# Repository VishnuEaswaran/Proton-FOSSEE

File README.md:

# Proton-FOSSEE

Proton is an arduino based development board with a battery of on-board sensors and actuators bundled with provisions for multiple communication technologies. Designed to be a one-stop solution for prototyping, it could serve as a playground for hardware novices as well as seasoned developers. 

P.S. : Proton ~~is~~ was  a project developed for FOSSEE of IIT bombay. The project is ~~in active development and thus watch this space for latest updates.~~ discontinued.

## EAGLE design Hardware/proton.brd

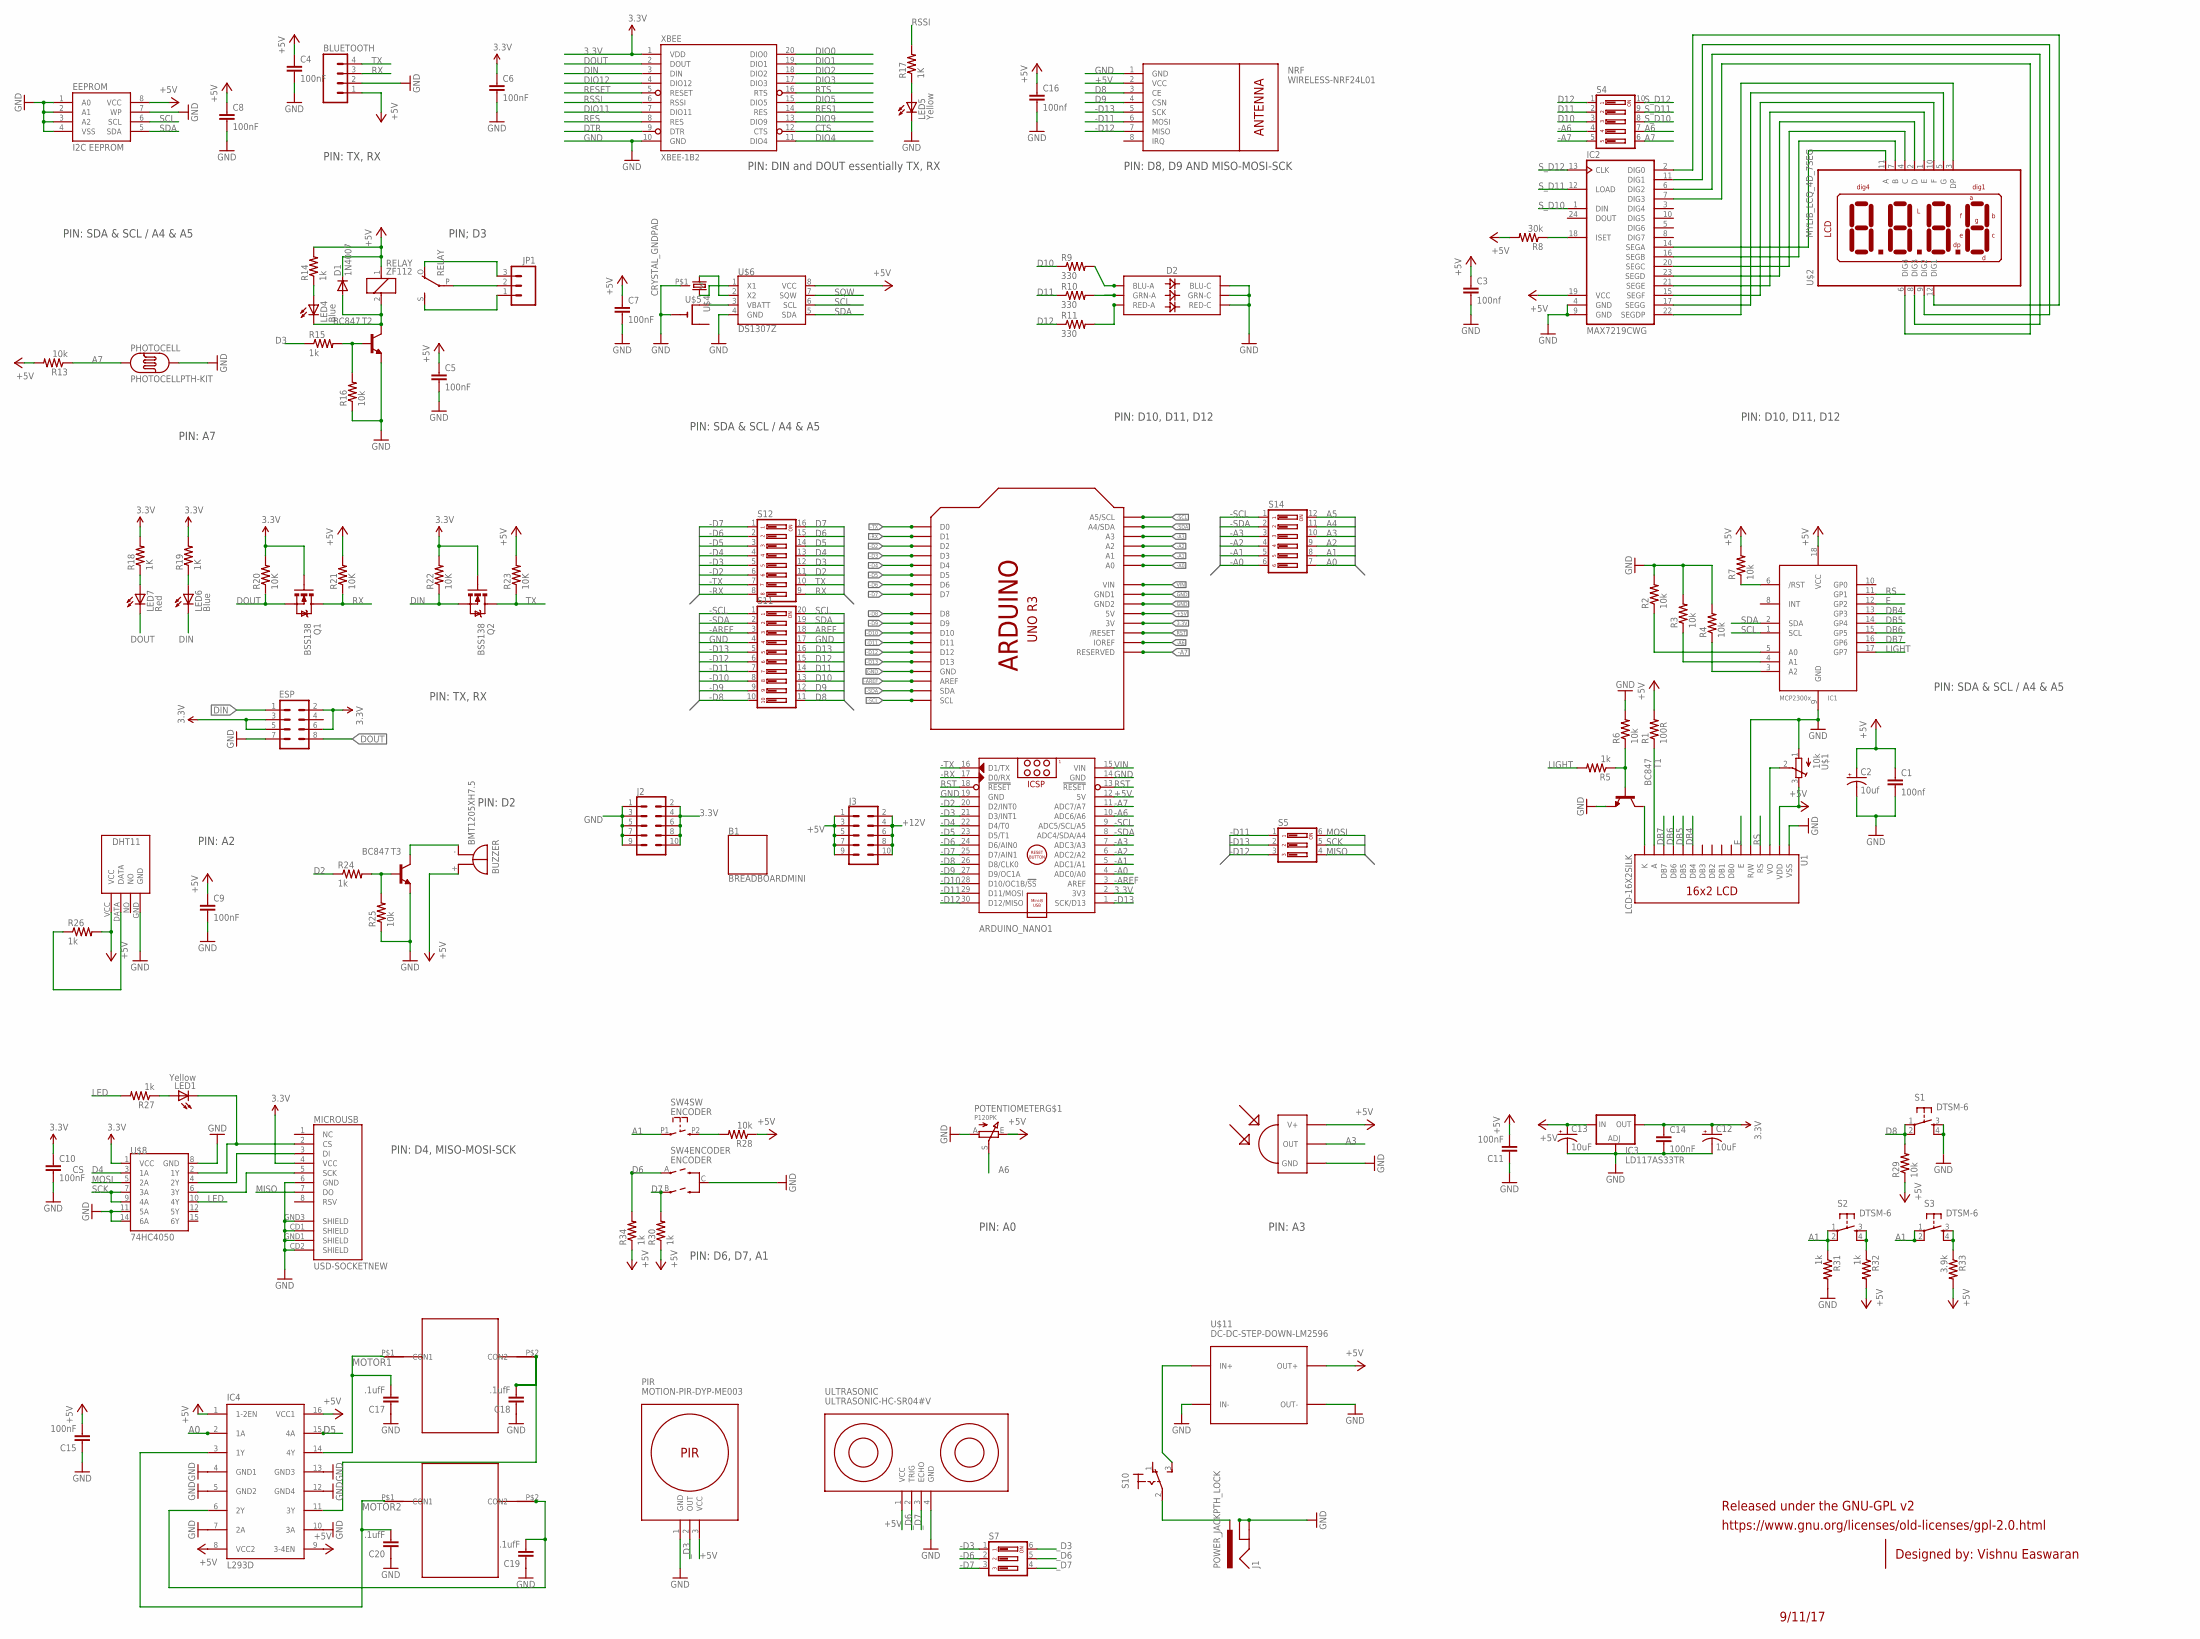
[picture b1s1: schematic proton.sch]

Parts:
ARDUINO_NANO1: ARDUINO_NANO
B1: BREADBOARDMINI; BREADBOARD-MINI
BLUETOOTH: M04PTH; 1X04
BUZZER: BMT1205XH7.5
C1, C3, C16: 100nf; 0805
C2: 10uf; EIA3216
C4, C5, C6, C7, C8, C9, C10, C11, C14, C15: 100nF; 0805
C12, C13: 10uF; EIA3216
C17, C18, C19, C20: .1ufF; 0805
D1: 1N4007; SMA-DIODE_ALT
D2: LED-RGBNO_IC; LED-TRICOLOR-5050
EEPROM: I2C EEPROM; SO08-EIAJ
ESP: M04X2; 2X4
IC1: MCP2300X/SO; SO18W
IC2: MAX7219CWG; SO24W
IC3: LD117AS33TR; SOT223
IC4: L293D; DIL16
IR: TSOP1730; TSOP17XX
J1: POWER_JACKPTH_LOCK; POWER_JACK_PTH_LOCK
J2, J3: CONN_05X2NO_SILK; 2X5_NOSILK
JP1: M03-SCREW-5MM; SCREWTERMINAL-5MM-3
LED1, LED5: Yellow; CHIPLED_0805
LED4, LED6: Blue; CHIPLED_0805
LED7: Red; CHIPLED_0805
MICROUSB: USD-SOCKETNEW; MICRO-SD-SOCKET-PP
MOTOR1, MOTOR2: TOY_MOTOR
NRF: WIRELESS-NRF24L01
PHOTOCELL: PHOTOCELLPTH-KIT; PHOTOCELL-KIT
PIR: MOTION-PIR-DYP-ME003
POTENTIOMETER: P120PK
Q1, Q2: BSS138; SOT23-3
R1: 100R; 0805
R2, R3, R4, R6, R7, R13, R16, R25, R28, R29: 10k; 0805
R5, R14, R15, R24, R26, R27, R30, R31, R32, R34: 1k; 0805
R8: 30k; 0805
R9, R10, R11: 330; 0805
R17, R18, R19: 1K; 0805
R20, R21, R22, R23: 10K; 0805
R33: 3.9k; 0805
RELAY: ZF112
S1, S2, S3: DTSM-6
S4: DIP05YL
S5, S7: DIP03YL
S10: M9040P
S11: DIP10YL
S12: DIP08YL
S14: DIP06YL
SW4: ENCODER; PEC12_INCREMENTAL_ENCODER
T1, T2, T3: BC847; SOT23-BEC
TEMPERATURESENSOR: DHT11
U1: LCD-16X2SILK; LCD-16X2
U$1: 10k; TC33X
U$2: MYLIB_LCQ_4D_7SEG; MYLIB_LDQ_4D_7SEG
U$4: CRYSTAL_GNDPAD; TC38H_GNDPAD
U$5: CR1220SMT; CR1220-SMD
U$6: DS1307Z; SO08-0.15
U$8: 74HC4050; SO016
U$11: DC-DC-STEP-DOWN-LM2596
U$14: UNO_R3
ULTRASONIC: ULTRASONIC-HC-SR04#V
XBEE: XBEE-1B2; XBEE-SILK

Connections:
3.3V: ARDUINO_NANO1.2 (3V3), C6.1, C10.1, C12.A (+), C14.1, ESP.2, ESP.3, ESP.5, ESP.6, IC3.4 (OUT), J2.2, J2.4, J2.6, J2.8, J2.10, MICROUSB.4 (VCC), Q1.1 (G), Q2.1 (G), R18.2, R19.2, R20.2, R22.2, U$8.1 (VCC), U$14.3V, XBEE.1 (VDD)
+5V: ARDUINO_NANO1.12 (5V), BLUETOOTH.1, BUZZER.+, C1.1, C2.A (+), C3.1, C4.1, C5.1, C7.1, C8.1, C9.1, C11.2, C13.A (+), C15.2, C16.1, D1.C, EEPROM.8 (VCC), IC1.18 (VCC), IC2.19 (VCC), IC3.3 (IN), IC4.1 (1-2EN), IC4.8 (VCC2), IC4.9 (3-4EN), IC4.16 (VCC1), IR.V+, J3.1, J3.3, J3.5, J3.7, J3.9, NRF.2 (VCC), PIR.3 (VCC), POTENTIOMETER.E, R1.2, R7.2, R8.2, R13.2, R14.2, R21.2, R23.2, R26.2, R28.1, R29.1, R30.1, R32.2, R33.2, R34.1, RELAY.1, TEMPERATURESENSOR.VCC, U1.2 (VDD), U$1.3 (E), U$6.8 (VCC), U$11.OUT+, U$14.5V, ULTRASONIC.1 (VCC)
+12V: J1.PWR, J3.2, J3.4, J3.6, J3.8, J3.10, S10.2
-A0: ARDUINO_NANO1.4 (ADC0/A0), S14.6, U$14.A0
-A1: ARDUINO_NANO1.5 (ADC1/A1), S14.5, U$14.A1
-A2: ARDUINO_NANO1.6 (ADC2/A2), S14.4, U$14.A2
-A3: ARDUINO_NANO1.7 (ADC3/A3), S14.3, U$14.A3
-A6: ARDUINO_NANO1.10 (ADC6/A6), S4.4, U$14.IOREF
-A7: ARDUINO_NANO1.11 (ADC7/A7), S4.5, U$14.RESERVED
-AREF: ARDUINO_NANO1.3 (AREF), S11.3, U$14.AREF
-D2: ARDUINO_NANO1.20 (D2/INT0), S12.6, U$14.D2
-D3: ARDUINO_NANO1.21 (D3/INT1), S7.1, S12.5, U$14.D3
-D4: ARDUINO_NANO1.22 (D4/T0), S12.4, U$14.D4
-D5: ARDUINO_NANO1.23 (D5/T1), S12.3, U$14.D5
-D6: ARDUINO_NANO1.24 (D6/AIN0), S7.2, S12.2, U$14.D6
-D7: ARDUINO_NANO1.25 (D7/AIN1), S7.3, S12.1, U$14.D7
-D8: ARDUINO_NANO1.26 (D8/CLK0), S11.10, U$14.D8
-D9: ARDUINO_NANO1.27 (D9/OC1A), S11.9, U$14.D9
-D10: ARDUINO_NANO1.28 (D10/OC1B/!SS), S11.8, U$14.D10
-D11: ARDUINO_NANO1.29 (D11/MOSI), NRF.6 (MOSI), S5.1, S11.7, U$14.D11
-D12: ARDUINO_NANO1.30 (D12/MISO), NRF.7 (MISO), S5.3, S11.6, U$14.D12
-D13: ARDUINO_NANO1.1 (SCK/D13), NRF.5 (SCK), S5.2, S11.5, U$14.D13
-RX: ARDUINO_NANO1.17 (D0/RX), S12.8, U$14.D1
-SCL: ARDUINO_NANO1.9 (ADC5/SCL/A5), S11.1, S14.1, U$14.A5 (A5/SCL), U$14.SCL
-SDA: ARDUINO_NANO1.8 (ADC4/SDA/A4), S11.2, S14.2, U$14.A4 (A4/SDA), U$14.SDA
-TX: ARDUINO_NANO1.16 (D1/TX), S12.7, U$14.D0
A0: IC4.2 (1A), S14.7
A1: R31.1, S2.1, S2.2, S3.1, S3.2, S14.8, SW4.P1 (1)
A2: R26.1, S14.9, TEMPERATURESENSOR.DATA
A3: IR.OUT, S14.10
A4: S14.11
A5: S14.12
A6: POTENTIOMETER.S, S4.7
A7: PHOTOCELL.1, R13.1, S4.6
AREF: S11.18
CTS: XBEE.12 (CTS)
D2: R24.1, S12.11
D3: R15.1, S12.12
D4: S12.13, U$8.3 (1A)
D5: IC4.15 (4A), S12.14
D6: R34.2, S12.15, SW4.A
D7: R30.2, S12.16, SW4.B
D8: NRF.3 (CE), R29.2, S1.1, S1.2, S11.11
D9: NRF.4 (CSN), S11.12
D10: R9.1, S4.3, S11.13
D11: R10.1, S4.2, S11.14
D12: R11.1, S4.1, S11.15
D13: S11.16
DB4: IC1.13 (GP3), U1.11 (DB4)
DB5: IC1.14 (GP4), U1.12 (DB5)
DB6: IC1.15 (GP5), U1.13 (DB6)
DB7: IC1.16 (GP6), U1.14 (DB7)
DIN: ESP.1, LED6.C, Q2.2 (S), R22.1, XBEE.3 (DIN)
DIO0: XBEE.20 (DIO0)
DIO1: XBEE.19 (DIO1)
DIO2: XBEE.18 (DIO2)
DIO3: XBEE.17 (DIO3)
DIO4: XBEE.11 (DIO4)
DIO5: XBEE.15 (DIO5)
DIO9: XBEE.13 (DIO9)
DIO11: XBEE.7 (DIO11)
DIO12: XBEE.4 (DIO12)
DOUT: ESP.8, LED7.C, Q1.2 (S), R20.1, XBEE.2 (DOUT)
DTR: XBEE.9 (DTR)
E: IC1.12 (GP2), U1.6 (E)
GND: ARDUINO_NANO1.14 (GND), ARDUINO_NANO1.19 (GND), BLUETOOTH.2, C1.2, C2.C (-), C3.2, C4.2, C5.2, C6.2, C7.2, C8.2, C9.2, C10.2, C11.1, C12.C (-), C13.C (-), C14.2, C15.1, C16.2, C17.1, C18.1, C19.1, C20.1, D2.4 (BLU-C), D2.5 (RED-C), D2.6 (GRN-C), EEPROM.1 (A0), EEPROM.2 (A1), EEPROM.3 (A2), EEPROM.4 (VSS), EEPROM.7 (WP), ESP.7, IC1.9 (GND), IC2.4 (GND), IC2.9 (GND), IC3.1 (ADJ), IC4.4 (GND1), IC4.5 (GND2), IC4.7 (2A), IC4.10 (3A), IC4.12 (GND4), IC4.13 (GND3), IR.GND, J1.GND, J1.GNDBREAK, J2.1, J2.3, J2.5, J2.7, J2.9, LED5.C, MICROUSB.6 (GND), MICROUSB.CD1 (SHIELD), MICROUSB.CD2 (SHIELD), MICROUSB.GND1 (SHIELD), MICROUSB.GND3 (SHIELD), NRF.1 (GND), PHOTOCELL.2, PIR.1 (GND), POTENTIOMETER.A, R2.2, R3.2, R4.2, R6.2, R16.1, R25.1, R31.2, S1.3, S1.4, S11.4, S11.17, SW4.C, T1.E, T2.E, T3.E, TEMPERATURESENSOR.GND, U1.1 (VSS), U1.5 (R/W), U$1.1 (A), U$4.P$1 (3), U$5.-, U$6.4 (GND), U$8.8 (GND), U$8.11 (5A), U$8.14 (6A), U$11.IN-, U$11.OUT-, U$14.GND, U$14.GND1, U$14.GND2, ULTRASONIC.4 (GND), XBEE.10 (GND)
LED: R27.2, U$8.10 (4Y)
LIGHT: IC1.17 (GP7), R5.2
MISO: MICROUSB.7 (DO), S5.4
MOSI: S5.6, U$8.5 (2A)
MOTOR1: C17.2, IC4.14 (4Y), MOTOR1.P$1 (CON1)
MOTOR2: C20.2, IC4.3 (1Y), MOTOR2.P$1 (CON1)
unnamed: C19.2, IC4.6 (2Y), MOTOR2.P$2 (CON2)
unnamed: S10.3 (S), U$11.IN+
unnamed: D2.3 (BLU-A), R9.2
unnamed: R32.1, S2.3, S2.4
unnamed: D2.2 (RED-A), R11.2
unnamed: D2.1 (GRN-A), R10.2
unnamed: R24.2, R25.2, T3.B
unnamed: C18.2, IC4.11 (3Y), MOTOR1.P$2 (CON2)
unnamed: R33.1, S3.3, S3.4
unnamed: JP1.3, RELAY.O
unnamed: BUZZER.-, T3.C
unnamed: LED4.A, R14.1
unnamed: R15.2, R16.2, T2.B
unnamed: D1.A, LED4.C, RELAY.2, T2.C
unnamed: JP1.2, RELAY.P
unnamed: JP1.1, RELAY.S
unnamed: IC1.5 (A0), R2.1
unnamed: IC1.4 (A1), R3.1
unnamed: IC1.3 (A2), R4.1
unnamed: R28.2, SW4.P2 (2)
unnamed: R5.1, R6.1, T1.B
unnamed: U1.3 (VO), U$1.2 (S)
unnamed: T1.C, U1.16 (K)
unnamed: U$4.1, U$6.2 (X2)
unnamed: U$5.+$1 (+), U$6.3 (VBATT)
unnamed: IC2.14 (SEGA), U$2.11 (A)
unnamed: MICROUSB.3 (DI), U$8.4 (2Y)
unnamed: MICROUSB.5 (SCK), U$8.6 (3Y)
unnamed: U$4.2, U$6.1 (X1)
unnamed: LED1.A, R27.1
unnamed: LED1.C, MICROUSB.2 (CS), U$8.2 (1Y)
unnamed: LED5.A, R17.1
unnamed: LED7.A, R18.1
unnamed: LED6.A, R19.1
unnamed: IC1.6 (/RST), R7.1
unnamed: IC2.18 (ISET), R8.1
unnamed: IC2.16 (SEGB), U$2.7 (B)
unnamed: IC2.20 (SEGC), U$2.4 (C)
unnamed: IC2.23 (SEGD), U$2.2 (D)
unnamed: IC2.21 (SEGE), U$2.1 (E)
unnamed: IC2.15 (SEGF), U$2.10 (F)
unnamed: IC2.17 (SEGG), U$2.5 (G)
unnamed: IC2.22 (SEGDP), U$2.3 (DP)
unnamed: IC2.7 (DIG3), U$2.6 (DIG4)
unnamed: IC2.6 (DIG2), U$2.8 (DIG3)
unnamed: IC2.11 (DIG1), U$2.9 (DIG2)
unnamed: IC2.2 (DIG0), U$2.12 (DIG1)
unnamed: R1.1, U1.15 (A)
RES: XBEE.8 (RES)
RES1: XBEE.14 (RES)
RESET: XBEE.5 (RESET)
RS: IC1.11 (GP1), U1.4 (RS)
RSSI: R17.2, XBEE.6 (RSSI)
RST: ARDUINO_NANO1.13 (!RESET), ARDUINO_NANO1.18 (!RESET), U$14.RESET (/RESET)
RTS: XBEE.16 (RTS)
RX: BLUETOOTH.3, Q1.3 (D), R21.1, S12.9
SCK: S5.5, U$8.7 (3A), U$8.9 (4A)
SCL: EEPROM.6 (SCL), IC1.1 (SCL), S11.20, U$6.6 (SCL)
SDA: EEPROM.5 (SDA), IC1.2 (SDA), S11.19, U$6.5 (SDA)
SQW: U$6.7 (SQW)
S_D10: IC2.1 (DIN), S4.8
S_D11: IC2.12 (LOAD), S4.9
S_D12: IC2.13 (CLK), S4.10
TX: BLUETOOTH.4, Q2.3 (D), R23.1, S12.10
VIN: ARDUINO_NANO1.15 (VIN), U$14.VIN
_D3: PIR.2 (OUT), S7.6
_D6: S7.5, ULTRASONIC.2 (TRIG)
_D7: S7.4, ULTRASONIC.3 (ECHO)

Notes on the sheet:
Released under the GNU-GPL v2
https://www.gnu.org/licenses/old-licenses/gpl-2.0.html
Designed by: Vishnu Easwaran
9/11/17
PIN: A7
PIN: D10, D11, D12
PIN: TX, RX
PIN: D8, D9 AND MISO-MOSI-SCK
PIN: SDA & SCL / A4 & A5
PIN: A0
PIN: D6, D7, A1
PIN: D4, MISO-MOSI-SCK
PIN: A2
PIN: D2
PIN: A3
PIN; D3
PIN: DIN and DOUT essentially TX, RX

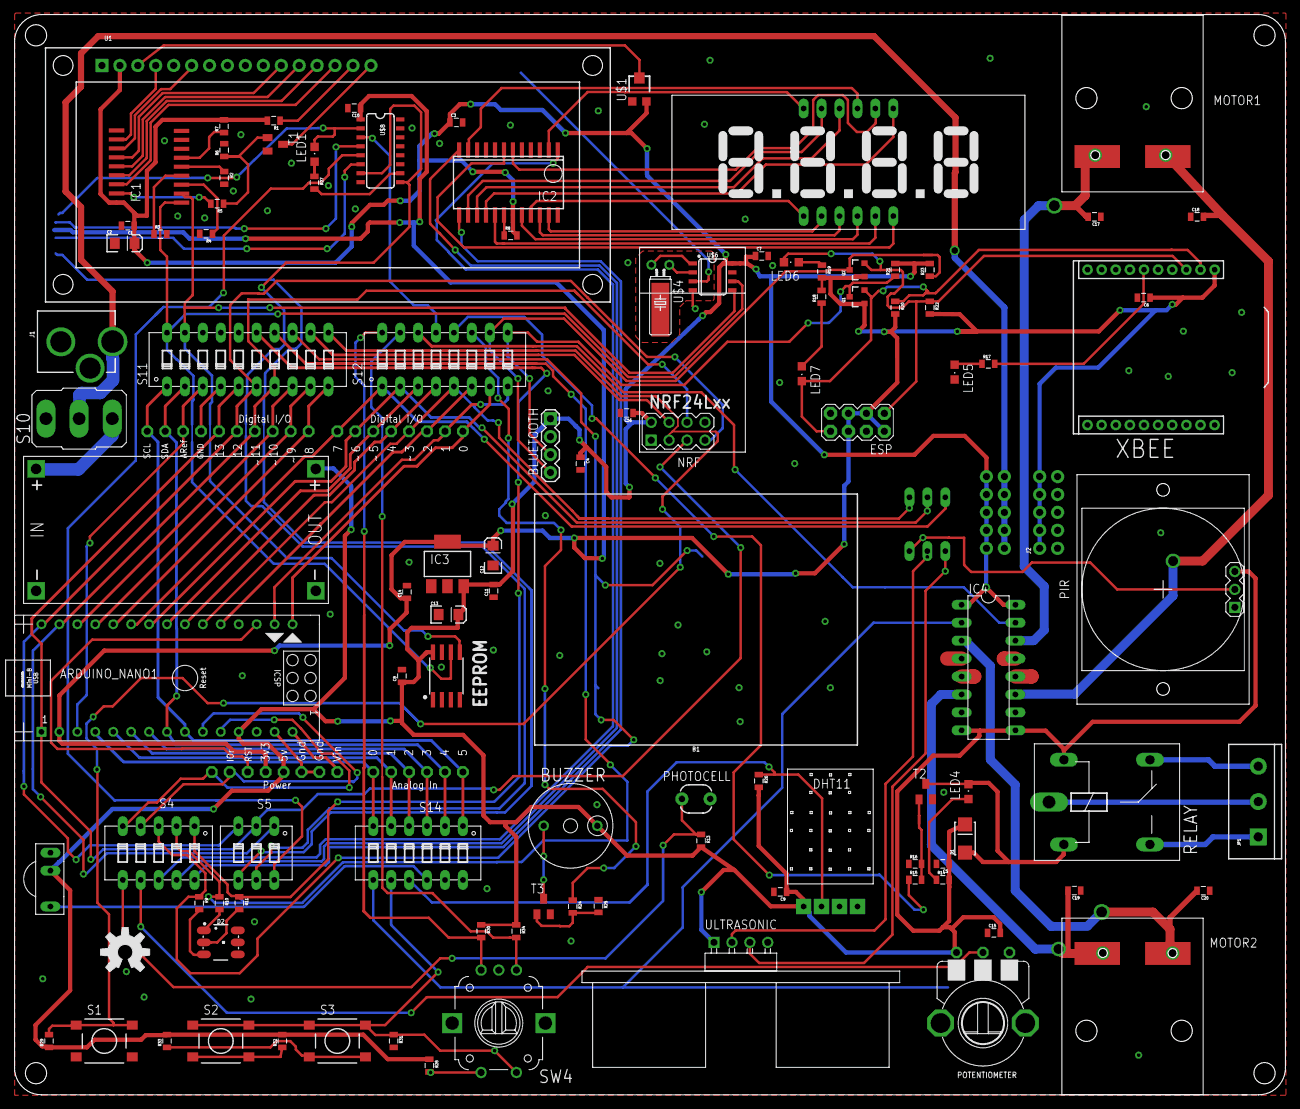
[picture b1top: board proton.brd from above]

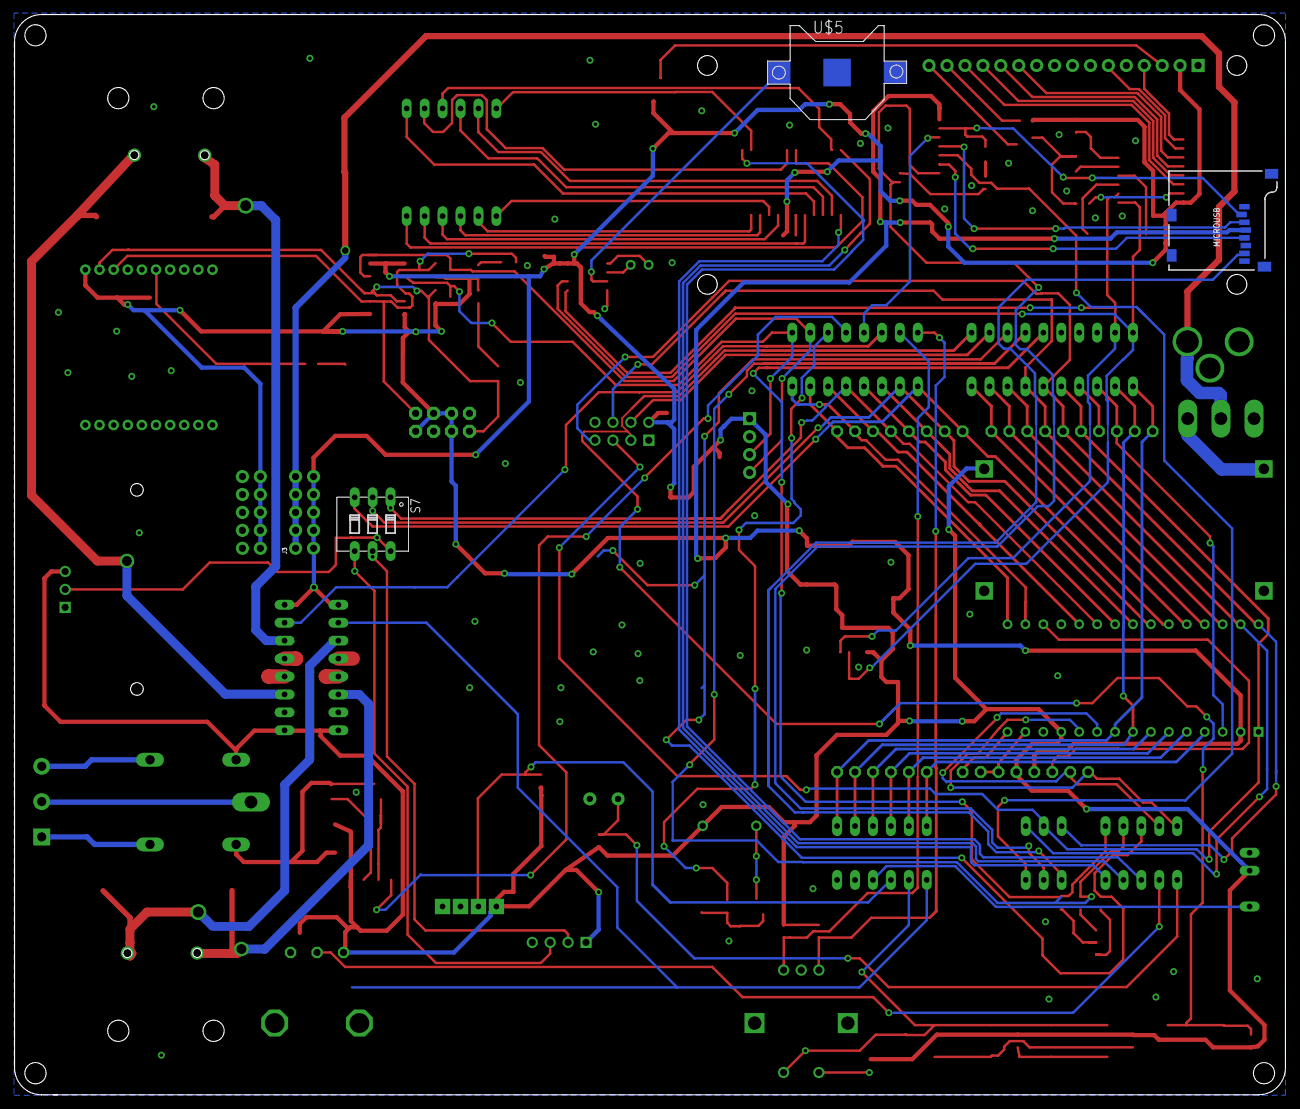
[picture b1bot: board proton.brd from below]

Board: 2 copper layers, 180.0 x 153.0 mm, 112 parts (4 on the bottom side), 120 nets.

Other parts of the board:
U$7: OSHW-LOGO-L

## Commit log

2017-12-05 updatedReadme
2017-12-05 V0.1
2017-12-12 Power rails and toggle switch
2017-12-26 properly sorted the pin-distributions, changed the motor drievr
2018-02-14 Fine tunings. Major change motor driver
2019-04-29 status update
2019-08-23 is -> was in README.

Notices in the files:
parts and their libraries:
SparkFun: Licensing: CC v3.0 Share-Alike You are welcome to use this library for commercial purposes.
SparkFun-Connectors: Licensing: Creative Commons ShareAlike 4.0 International - https://creativecommons.org/licenses/by-sa/4.0
